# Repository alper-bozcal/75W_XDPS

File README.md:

# DBC2-Battery-Charger

  Main repository for the DEIF Battery Charger - 2 products.

## Dosyalama Sistemi

`Develop` branchinde kodun çalışma garantisi yoktur fakat en son kod bulunabilir. `Main` branch' de versiyon atlatıldığında stabil kod bulunabilir.

Yazılım `Firmware` klasöründe tutulmaktadır. `Common/` tüm ürünler için ortak fonksiyonları içermektedir. Bunun yanında yer alan klasörler ise proje ismine göre ayrılmıştır.

`ENKO` ve `Documents` klasörleri geliştirme sırasında oluşturulan dökümanları tutmaktadır. Bunları bazıları müşteri ile paylaşılmıştır.

`Hardware/` donanım şema ve PCB dosyalarını içermektedir.

`Simulations` ve `Tests` klasörleri donanım için gerekli çalışmalarda oluşturulan dosyaları içermektedir. Test sonuçları `Tests/` içerisinde bulunabilir.

## Algoritma

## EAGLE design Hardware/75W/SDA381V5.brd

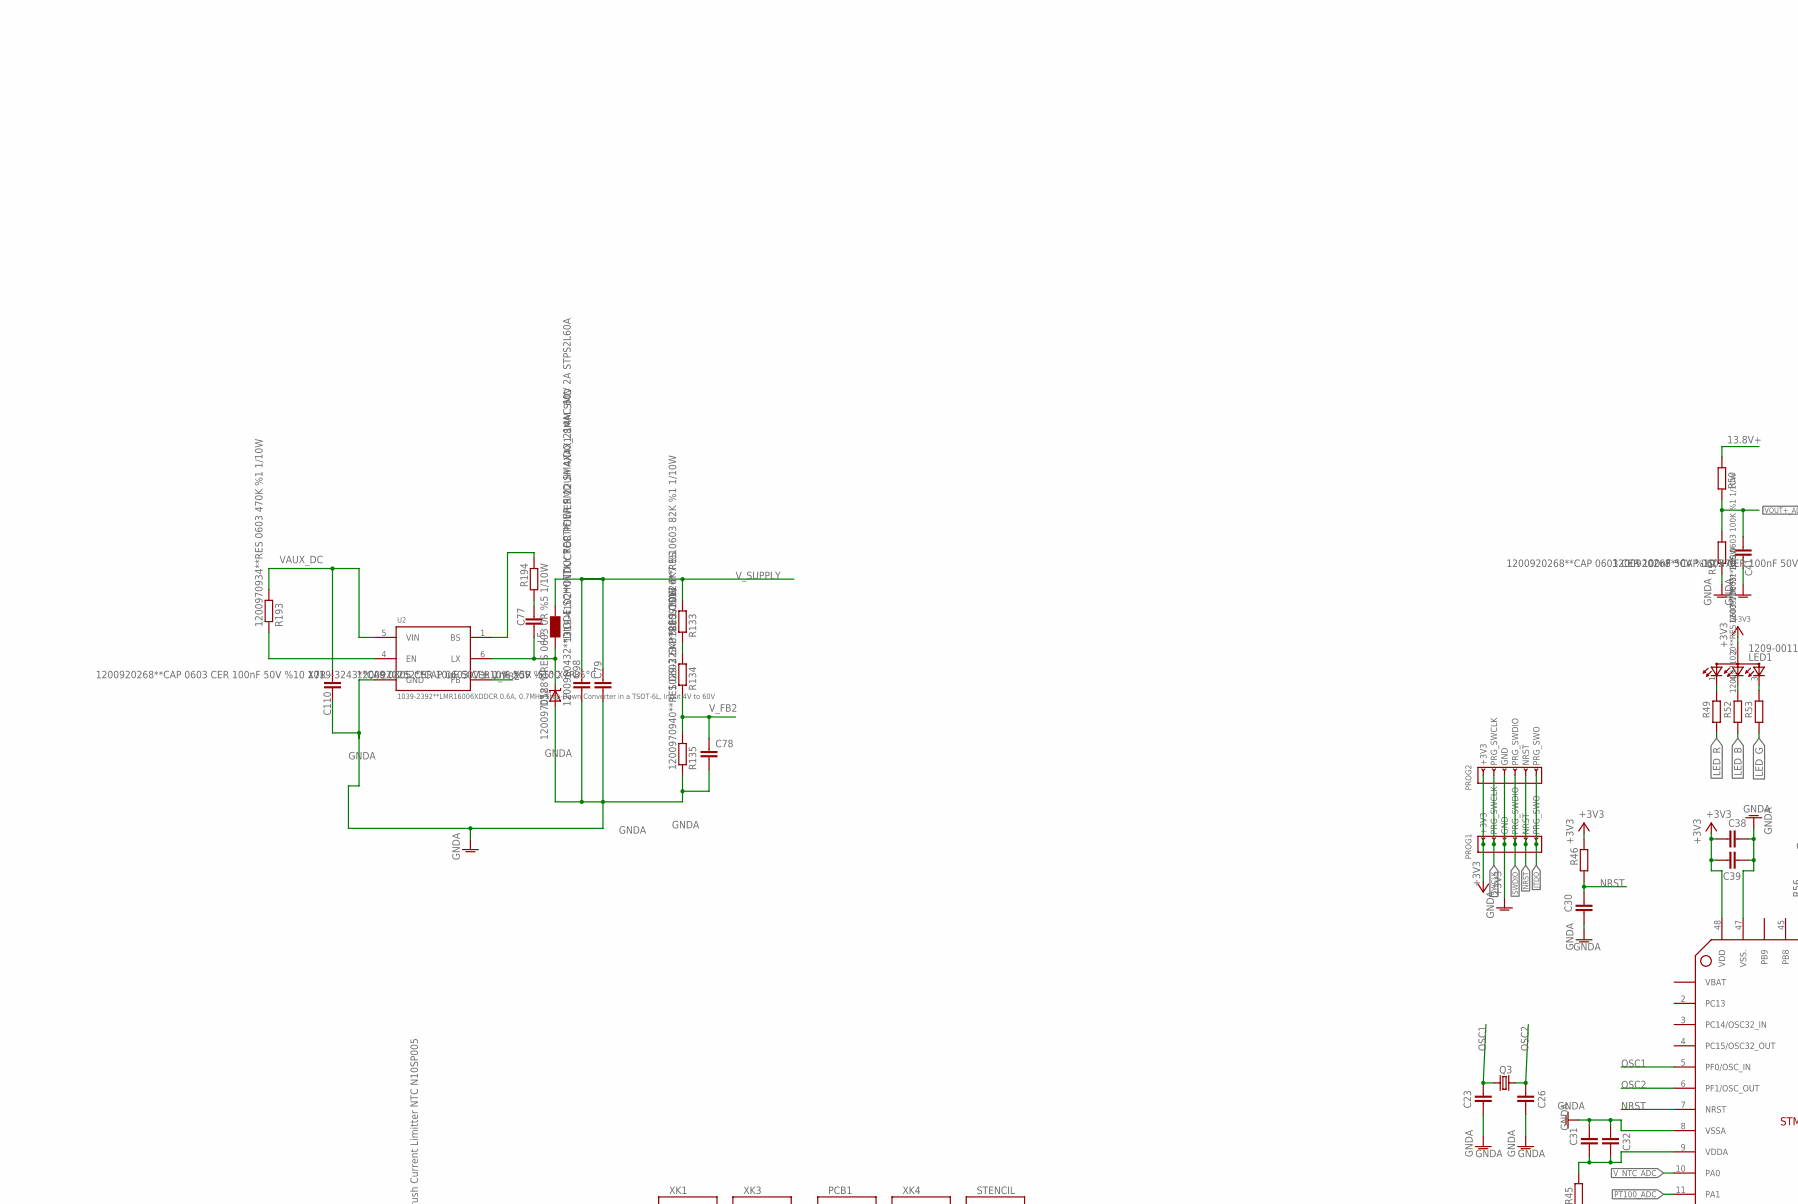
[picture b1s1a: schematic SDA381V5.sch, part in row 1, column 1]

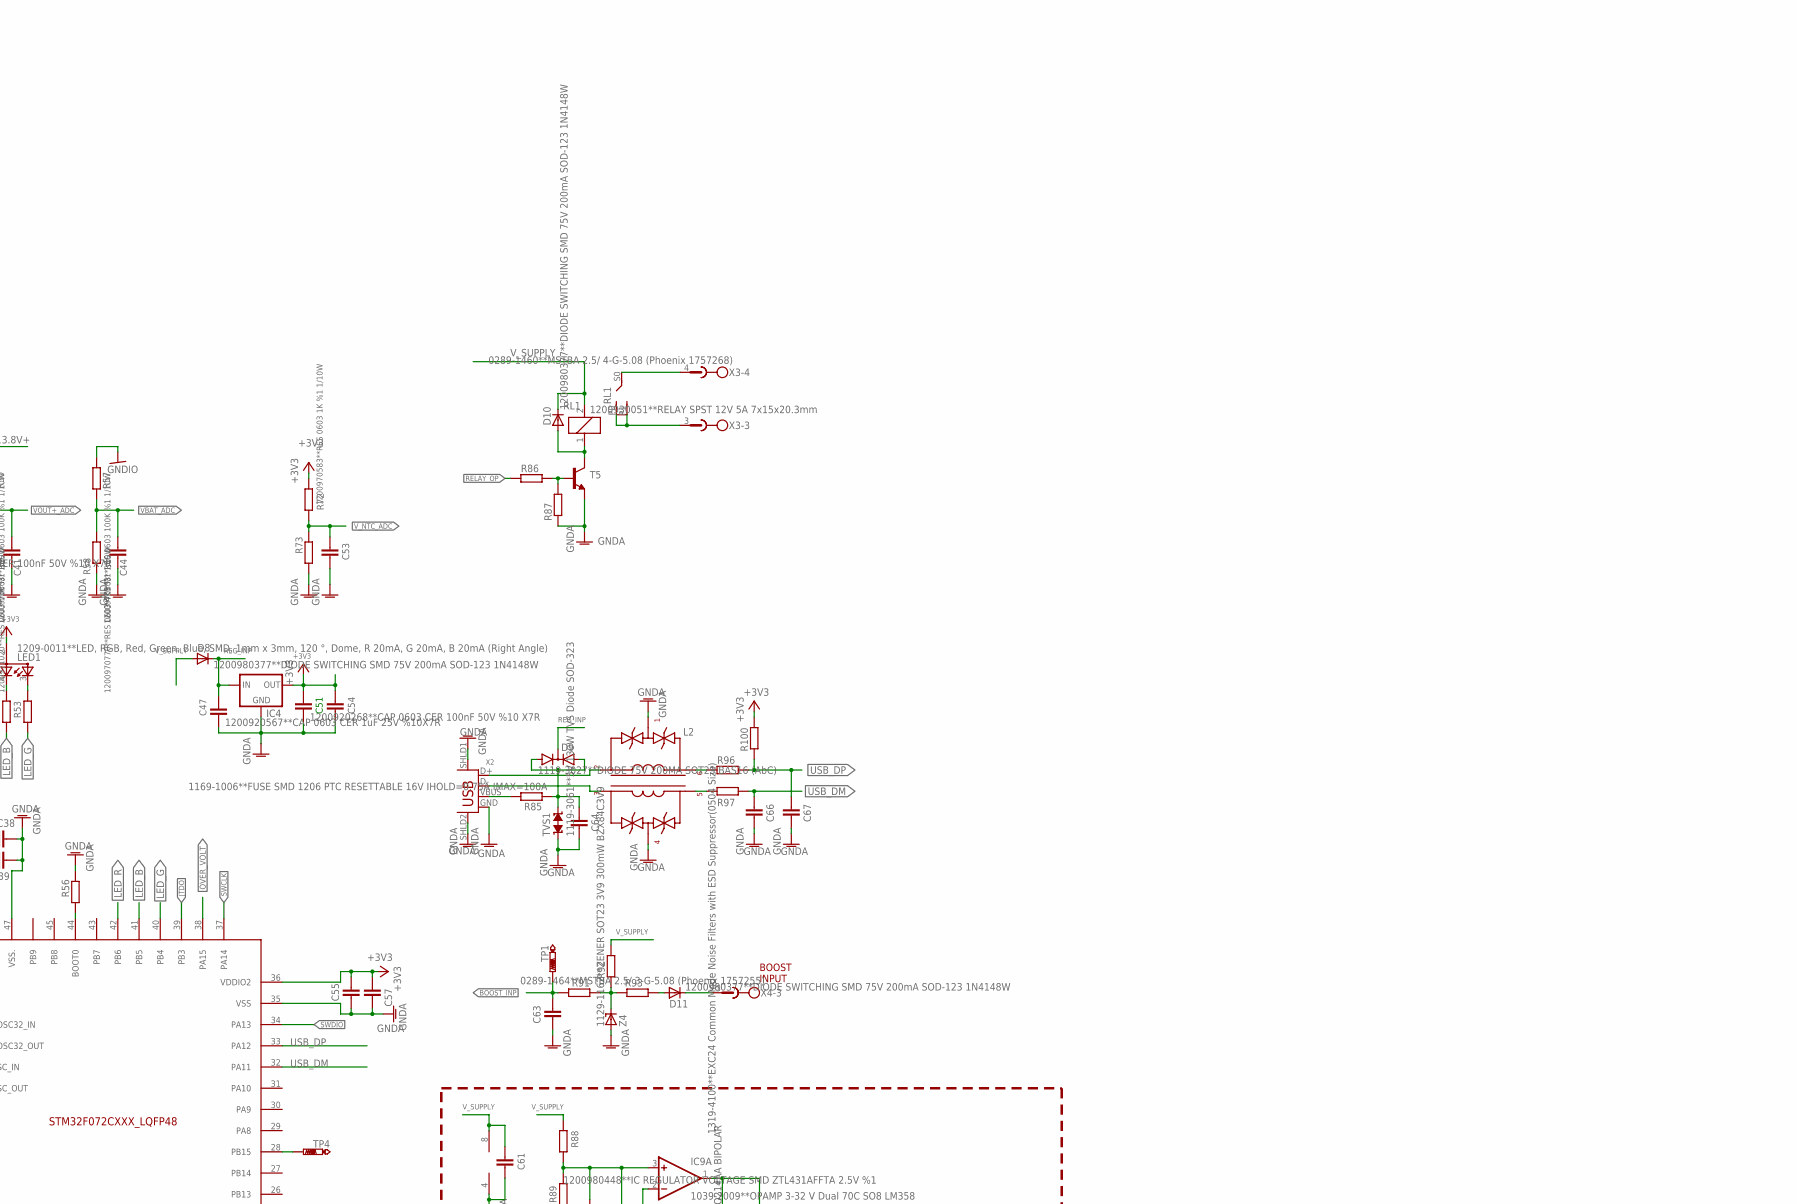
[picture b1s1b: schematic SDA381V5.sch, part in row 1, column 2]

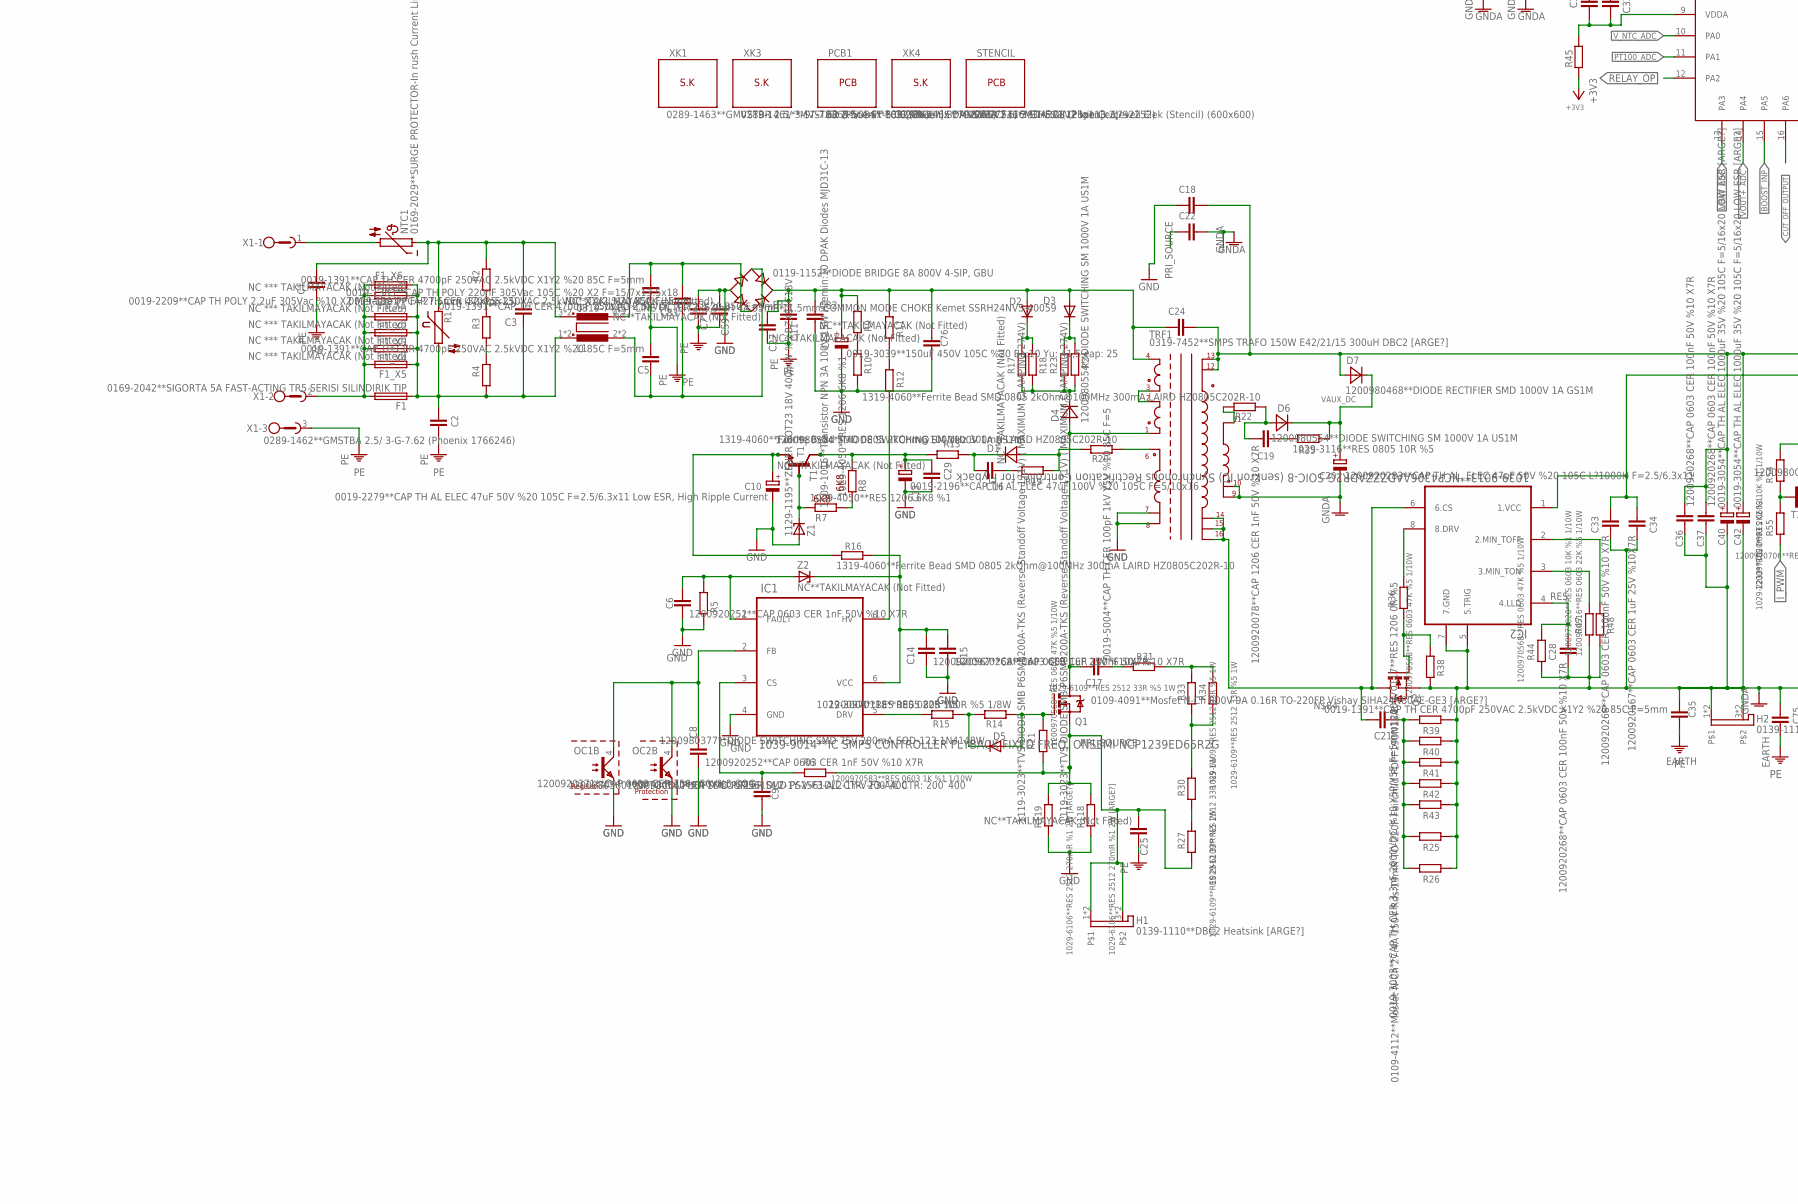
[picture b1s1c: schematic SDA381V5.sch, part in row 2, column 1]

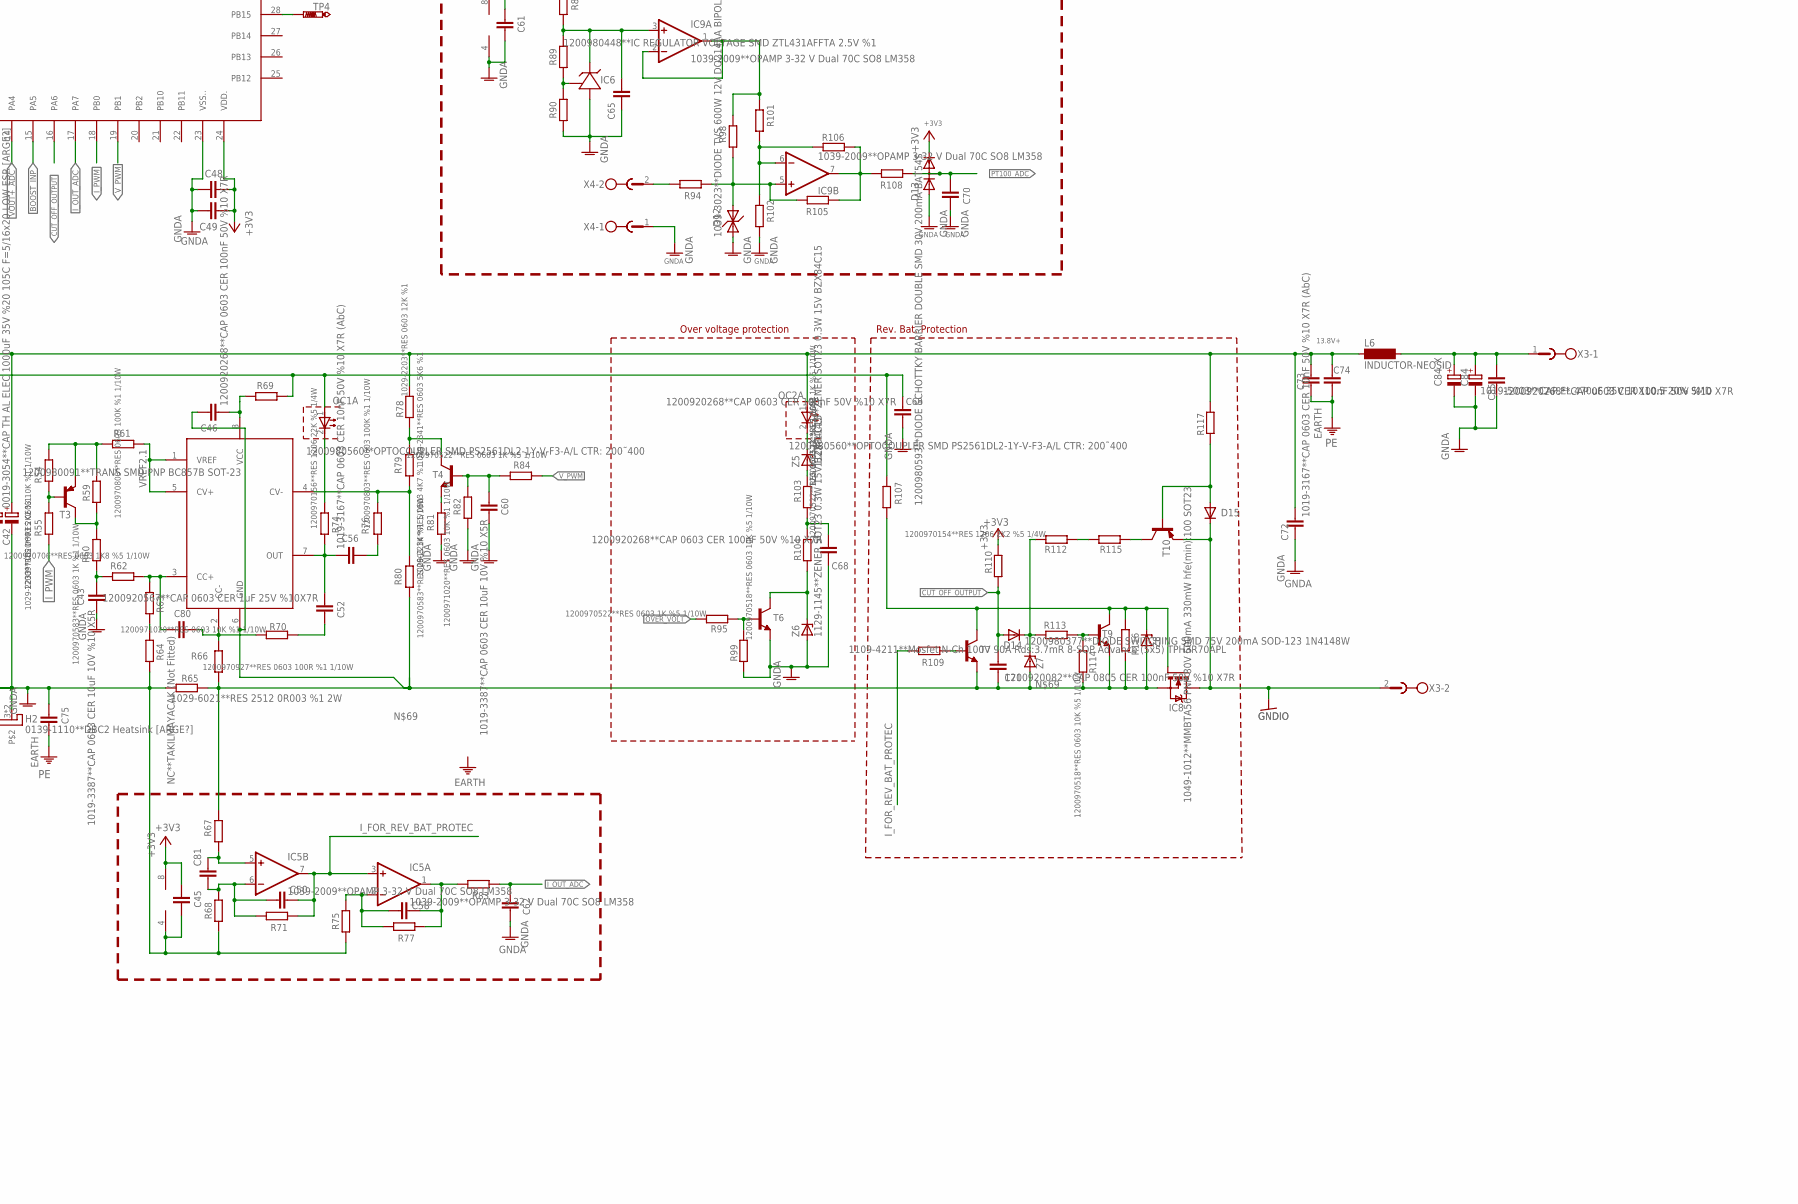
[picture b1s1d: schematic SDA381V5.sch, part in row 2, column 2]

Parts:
B1: 0119-1152**DIODE BRIDGE 8A 800V 4-SIP, GBU; DıODE_BRIDGE_8A_DIK
C1, C2, C25, C27, C59: NC**TAKILMAYACAK (Not Fitted); C50-035X75
C3: 0019-2209**CAP TH POLY 2.2uF 305Vac %10 X2 Metali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; C275-113X316_&_C150-072X183_&_C225-113X268
C4, C5, C7, C11: 0019-1391**CAP TH CER 4700pF 250VAC 2.5kVDC X1Y2 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; C50-035X75
C6, C8, C98: 1200920252**CAP 0603 CER 1nF 50V %10 X7R; C0603_ENKO
C9, C58: 1200920371**CAP 0603 CER 150p 50V%5 COG; C0603_ENKO
C10: 0019-2279**CAP TH AL ELEC 47uF 50V %20 105C F=2.5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; E2,5-7
C12: 0019-3039**150uF 450V 105C %20 Ba:10 Yu: 41,5 çap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; EB25D
C13: 0019-2196**CAP TH AL ELEC 47uF 100V %20 105C F=5/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; E5-10,5
C14, C34, C47, C52: 1200920567**CAP 0603 CER 1uF 25V %10X7R; C0603_ENKO
C15, C28, C30, C31, C33, C36, C37, C38, C41, C44, C45, C46, C49, C51, C53, C57, C61, C62, C64, C65, C68, C69, C70, C77, C85, C110: 1200920268**CAP 0603 CER 100nF 50V %10 X7R; C0603_ENKO
C16, C29: NC**TAKILMAYACAK (Not Fitted); C1206_ENKO
C17: 0019-5004**CAP TH CER 100pF 1kV Y5V %10 85C F=5; C075-32X103/C050-035X75
C18: 1200920292**CAP TH CER 2.2nF 300Vac %20 X1Y2 F=7.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; C075-32X103_DEIF
C19: 1200920078**CAP 1206 CER 1nF 50V %10 X7R; C1206_ENKO
C20: 1200920283**CAP TH AL. ELEC 47uF 50V %20 105C L?1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; E2,5-7
C21: 0019-3003**CAP TH CER 3.3nF 2000VDC %10 Y5P/Y5E F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; C050-045X075
C22, C24: NC**TAKILMAYACAK (Not Fitted); C075-32X103_DEIF
C23, C26: 1019-3352**CAP 0603 CER 22pF 50V %5 NPO; C0603_ENKO
C32, C39, C48, C55, C56, C63, C72: 1019-3167**CAP 0603 CER 10nF 50V %10 X7R (AbC); C0603_ENKO
C35: 0019-1391**CAP TH CER 4700pF 250VAC 2.5kVDC X1Y2 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; C050-045X075
C40: 0019-3054**CAP TH AL ELEC 1000uF 35V %20 105C F=5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; E5-13/E7,5-16
C42: 0019-3054**CAP TH AL ELEC 1000uF 35V %20 105C F=5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; E5-13
C43, C60: 1019-3387**CAP 0603 CER 10uF 10V %10 X5R; C0603_ENKO
C50, C80, C81: NC**TAKILMAYACAK (Not Fitted); C0603_ENKO
C54: 1019-3301**CAP 0805 47uF 6.3V %20 X5R; C0805_ENKO
C66, C67: 1019-3381**CAP 0603 CER 33pf 50V %5 NPO(COG); C0603_ENKO
C71: 1200920082**CAP 0805 CER 100nF 50V %10 X7R; C0805_ENKO
C73: 0019-1391**CAP TH CER 4700pF 250VAC 2.5kVDC X1Y2 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; C050-035X075
C74, C75: NC**TAKILMAYACAK (Not Fitted); C050-035X075
C76: NC**TAKILMAYACAK (Not Fitted); C065-052X106
C78: 1200920271**CAP 0603 CER 10pF 50V%10 COG; C0603_ENKO
C79: 1019-3243**CAP 0805 CER 10uF 50V ±10% X5R -55°C ~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; C0805_ENKO
C82: NC**TAKILMAYACAK (Not Fitted); C150-091X182
C83: 0019-1383**CAP TH POLY 220nF 305Vac 105C %20 X2 F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; C150-091X182_C225-108X268
C84: 1019-5003**CAP.EL.470uF 35V 10X10.5 20% SMD; E5-10,5
C84_X: CPOL-EUE2.5-7; E2,5-7
D1, D4, D6: 1200980554**DIODE SWITCHING SM 1000V 1A US1M; M7_DC_DIYOT
D2, D3: 1119-3023**TVS DIODE SMB P6SMB200A-TKS (Reverse S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; SMB
D5, D8, D10, D11, D14, D15: 1200980377**DIODE SWITCHING SMD 75V 200mA SOD-123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; SOD123
D7: 1200980468**DIODE RECTIFIER SMD 1000V 1A GS1M; M7_DC_DIYOT
D9: 1119-3027**DIODE 75V 200MA SOT23 BAS16 (AbC); SOT23
D12: 1039-3023**DIODE TVS 600W 12V DO214AA BIPOLAR; TRANSIL_SMB
D13: 1200980593**DIODE SCHOTTKY BARRIER DOUBLE SMD 30V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; SOT23
D18: 1200980432**DIODE SCHOTTKY RECTIFIER SMD SMA/DO_2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; SMA
F1: 0169-2042**SIGORTA 5A FAST-ACTING TR5 SERISI SILI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; SENS_FUSE
F1_X1: NC *** TAKILMAYACAK (Not Fitted); FUSE_0678D
F1_X2: NC *** TAKILMAYACAK (Not Fitted); FUSE_1025FA
F1_X3: NC *** TAKILMAYACAK (Not Fitted); FUSE_EBF_FUSE_446/447
F1_X4: NC *** TAKILMAYACAK (Not Fitted); FUSE_OMF250
F1_X5: NC *** TAKILMAYACAK (Not Fitted); FUSE_UMF250
F1_X6: FUSE_TYPE0679H
H1, H2: 0139-1110**DBC2 Heatsink [ARGE?]; DEIF_SOGUTUCU_2
IC1: 1039-9014**IC SMPS CONTROLLER FLYBACK FIXED FREQ.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; NCP1239_SMPS_IC
IC2: 1039-9013**NCP4306AADZZZADR2G SOIC-8 (senkron IC)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; NCP4306
IC3: 1039-2224**TSM1011ID SO-8 Constant Voltage and Co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; SO-8
IC4: 1039-3003**Voltage Regulator SOT-89 3.3V Diodes A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; SOT89
IC5, IC9: 1039-2009**OPAMP 3-32 V Dual 70C SO8 LM358; SO08
IC6: 1200980448**IC REGULATOR VOLTAGE SMD ZTL431AFFTA 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; TL431_SOT23F
IC8: 1109-4211**Mosfet N-Ch 100V 90A Rds:3.7mR 8-SOP A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; TPH6R30ANL
L1: 0319-7445**LINE FILTER 2x5,9mH 4A 55mR 11.5mm COM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; UU1620_&_FWCMET24V
L2: 1319-4100**EXC24 Common Mode Noise Filters with E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; EXC24CS_COMMON_MODE
L5: 1319-4102**INDUCTOR POWER 22UH 4X4X1.8MM SMD; WE-PD2_5MM
L6: INDUCTOR-NEOSID
LED1: 1209-0011**LED, RGB, Red, Green, Blue, SMD, 1mm x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; KPFA-3010RGBC-11
NTC1: 0169-2029**SURGE PROTECTOR-In rush Current Limitt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; NTC_15R_2A_&_N15SP005-5
OC1, OC2: 1200980560**OPTOCOUPLER SMD PS2561DL2-1Y-V-F3-A/L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; PS2561DL2-1_OPTO1
PCB1: 0369-5034**PCB [ARGE?] SDA381V2CF416M3HFS2(123x11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; PCB
PROG1, PROG2: NC**TAKILMAYACAK (Not Fitted); PROG_6PIN
Q1: 0109-4091**Mosfet N-Ch 800V 9A 0.16R TO-220FP Vis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; TO220BV
Q2: 0109-4112**Mosfet N-Ch 27.4A 150V Rds:19mR TO-220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; TO220BV
Q3: 1149-0006**HC49S SMD KRISTAL 8MHZ -40+85 20PF 50P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; HC49UP
R1: 0169-2013**Varistor 20mm 300V; S20K40
R2, R3, R4: 1200970587**RES 1206 470K %5 1/4W; R1206_ENKO
R5: 1200970687**RES 0603 56K %1 1/10W; R0603_ENKO
R6, R60, R61, R72, R75, R81, R89, R102: 1200970583**RES 0603 1K %1 1/10W; R0603_ENKO
R7, R8: 1029-4050**RES 1206 6K8 %1; R1206_ENKO
R9, R10: 1200970179**RES 1206 330K %5 1/4W; R1206_ENKO
R11, R12, R112: 1200970154**RES 1206 2K2 %5 1/4W; R1206_ENKO
R13: 1200970601**RES 1206 10R %5 1/4W; R1206_ENKO
R14: 1200970118**RES 0805 100R %5 1/8W; R0805_ENKO
R15: 1029-3008**RES 0805 22R %5; R0805_ENKO
R16, R20, R22, R45: 1319-4060**Ferrite Bead SMD 0805 2kOhm@100MHz 300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; R0805_ENKO
R17, R18, R23, R24: 1029-3146**RES 1206 7R68 %1; R1206_ENKO
R19: NC**TAKILMAYACAK (Not Fitted); R1206_ENKO
R21, R38, R44, R92: 1200970568**RES 0603 47K %5 1/10W; R0603_ENKO
R25, R26, R39, R40, R41, R42, R43: 1200970228**RES 1206 47R %5 1/4W; R1206_ENKO
R27, R30, R31, R33, R34: 1029-6109**RES 2512 33R %5 1W; R2512
R35, R69: 1029-3116**RES 0805 10R %5; R0805_ENKO
R36: 1200970117**RES 1206 0R %5; R1206_ENKO
R46, R87, R91, R99, R109, R114: 1200970518**RES 0603 10K %5 1/10W; R0603_ENKO
R47, R51, R54, R70, R82: 1200971020**RES 0603 10K %1 1/10W; R0603_ENKO
R48, R110: 1200970516**RES 0603 22K %5 1/10W; R0603_ENKO
R49, R52, R53: 1029-2005**RES 0603 220R %1; R0603_ENKO
R50, R57, R59, R76: 1200970803**RES 0603 100K %1 1/10W; R0603_ENKO
R55: 1029-2233**RES 0603 2K2 %1; R0603_ENKO
R56, R67, R68, R83, R84, R86, R95, R103, R104: 1200970522**RES 0603 1K %5 1/10W; R0603_ENKO
R58: 1200970770**RES 0603 4K3 %1 1/10W; R0603_ENKO
R62: 1200970706**RES 0603 1K8 %5 1/10W; R0603_ENKO
R63: 1029-2003**RES 0603 10R %1; R0603_ENKO
R64: 1029-2006**RES 0603 47R %1; R0603_ENKO
R65: 1029-6021**RES 2512 0R003 %1 2W; R2512
R66: 1200970927**RES 0603 100R %1 1/10W; R0603_ENKO
R71, R80, R88, R98, R134: 1029-2234**RES 0603 4K7 %1; R0603_ENKO
R73: 1169-1001**TSM2A103F3951RZ THINKING 0805 10K NTC 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; R0805_ENKO
R74: 1200970156**RES 1206 22K %5 1/4W; R1206_ENKO
R77: 1029-6089**RES 0603 6K8 %5; R0603_ENKO
R78: 1029-2203**RES 0603 12K %1; R0603_ENKO
R79: 1029-2341**RES 0603 5K6 %1; R0603_ENKO
R85: 1169-1006**FUSE SMD 1206 PTC RESETTABLE 16V IHOLD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; R1206_ENKO
R90: 1029-2231**RES 0603 1K8 %1; R0603_ENKO
R93: 1409-0025**RES 0603 470R %5 1/16W; R0603_ENKO
R94, R96, R97: 1029-6086**RES 0603 22R %1; R0603_ENKO
R100: 1200970852**RES 0603 1K5 %5 1/10W ( <-1029-3501 ); R0603_ENKO
R101: 1200970684**RES 0603 47K %1 1/10W; R0603_ENKO
R105: 1029-2229**RES 0603 120K %1; R0603_ENKO
R106: 1029-2219**RES 0603 30K %1; R0603_ENKO
R107: 1200970515**RES 0603 100K %5 1/10W; R0603_ENKO
R108: 1200970730**RES 0603 560R %1 1/10W; R0603_ENKO
R113: 1200970121**RES 0805 1K %5 1/8W; R0805_ENKO
R115: 1200970853**RES 1206 39K %1 1/4W; R1206_ENKO
R116: 1200970585**RES 0603 1M %5 1/10W; R0603_ENKO
R117: 1029-6015**RES 1206 56K %5; R1206_ENKO
R118, R119: 1029-6106**RES 2512 270mR %1 2W [ARGE?]; R2512
R133: 1200970626**RES 0603 82K %1 1/10W; R0603_ENKO
R135: 1200970940**RES 0603 6K8 %1 1/10W; R0603_ENKO
R193: 1200970934**RES 0603 470K %1 1/10W; R0603_ENKO
R194: 1200970528**RES 0603 0R %5 1/10W; R0603_ENKO
RL1: 1200930051**RELAY SPST 12V 5A 7x15x20.3mm; ALD1_AND_ALJ_RELAY
STENCIL: 041-7516**SDA381V2 için Çerçeveli Elek (Stencil) 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; PCB
T1: 1109-1016**Transistor NPN 3A 100V 15W Hfemin:10 D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; DPAK
T1_X, T4, T5, T6, T7, T9: 1200980090**TRANS SMD NPN BC847B SOT-23; SOT23
T3: 1200980091**TRANS SMD PNP BC857B SOT-23; SOT23-BEC
T10: 1049-1012**MMBTA56 PNP 80V 500mA 330mW hfe(min):1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; SOT23-BEC
TP1, TP4: PTR1TP20R; TP20R
TRF1: 0319-7452**SMPS TRAFO 150W E42/21/15 300uH DBC2 [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; DEIF_TRF
TVS1: 1119-3061**5V 130W TVS Diode SOD-323; SOD323
U1: 1039-2220**STM32F072C8T6 64K Flash USB, CAN; STM32F072CXXX_LQFP48
U2: 1039-2392**LMR16006XDDCR 0.6A, 0.7MHz Step-Down C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; AOZ1282CI-1
X1: 0289-1462**GMSTBA 2.5/ 3-G-7.62 (Phoenix 1766246); GMSTBA3
X2: 0309-1064**USB Type-B Mini Connector Horizantal; USB_B(YATIK)
X3: 0289-1460**MSTBA 2.5/ 4-G-5.08 (Phoenix 1757268); MSTBA4
X4: 0289-1464**MSTBA 2.5/ 3-G-5.08 (Phoenix 1757255); MSTBA3
XK1: 0289-1463**GMVSTBR 2.5/ 3-ST-7.62 (Phoenix 183253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; SOKET
XK3: 0289-1461**MVSTBR 2.5/ 4-ST-5.08 (Phoenix 1792265); SOKET
XK4: 0289-1465**MVSTBR 2.5/ 3-ST-5.08 (Phoenix 1792252); SOKET
Z1: 1129-1195**ZENER SOT23 18V 400mW %5 BZX84C18V; SOT23
Z2: NC**TAKILMAYACAK (Not Fitted); SOT23
Z4: 1129-1162**ZENER SOT23 3V9 300mW BZX84C3V9; SOT23
Z5, Z6: 1129-1145**ZENER SOT23 0.3W 15V BZX84C15; SOT23
Z7: 1129-1151**ZENER SOT23 12V 225mW BZX84C12; SOT23
Z8: 1129-1140**ZENER SOT23 5V1 0.4W BZX84C5V1; SOT23

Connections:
13.8V+: C18.P$1 (1), C24.P$1 (1), C36.1, C37.1, C40.+, C40.+1 (+), C42.+, C72.2, C73.1, C74.1, D7.A, L6.1, OC2.1, R50.1, R78.2, R117.1, TRF1.9 (12), TRF1.10 (13), TRF1.21 (13), TRF1.22 (12), TRF1.29 (12), TRF1.30 (13), TRF1.43 (12), TRF1.44 (13)
+3V3: C38.1, C39.1, C45.1, C48.1, C49.1, C51.1, C54.1, C55.1, C57.1, D13.2 (C), IC4.3 (OUT), IC5.8 (V+), LED1.2, PROG1.1 (+3V3), PROG2.1 (+3V3), R45.2, R46.1, R72.2, R100.2, R110.2, U1.24 (VDD.), U1.36 (VDDIO2), U1.48 (VDD)
AUX1: D1.A, R19.2, R20.2
BOOST_INP: C63.1, R91.1, TP1.TP, U1.15 (PA5)
CUT_OFF_OUTPUT: C71.1, D14.A, R110.1, U1.16 (PA6)
DRAIN1: C17.1, C17.3 (1), D4.A, Q1.D, TRF1.55 (1), TRF1.56 (1), TRF1.57 (1), TRF1.58 (1)
FB: C8.1, IC1.2 (FB), OC1.4, OC2.4
GATE1: IC8.GATE (G4), R107.1, R116.2, T7.3 (C), T9.3 (C), Z8.3 (C)
GND: B1.-, C6.2, C7.2, C8.2, C9.1, C10.-, C12.-, C13.-, C14.2, C15.2, C18.P$2 (2), C29.1, C59.2, C76.2, C82.2, IC1.4 (GND), OC1.3, OC2.3, R5.1, R10.1, R118.1, R119.1, TRF1.6 (7), TRF1.14 (7), TRF1.33 (7), TRF1.48 (8), TRF1.49 (7), Z1.1 (A)
GNDA: C20.-, C22.P$1 (1), C23.2, C26.2, C28.1, C30.1, C31.2, C32.2, C33.1, C34.1, C35.1, C36.2, C37.2, C38.2, C39.2, C40.-, C40.-1 (-), C41.2, C42.-, C43.1, C44.2, C45.2, C47.2, C48.2, C49.2, C51.2, C53.2, C54.2, C55.2, C57.2, C60.1, C61.2, C62.1, C63.2, C64.2, C65.1, C66.2, C67.2, C68.1, C69.1, C70.1, C72.1, C75.2, C78.2, C79.1, C84.-, C84_X.-, C85.2, C98.1, C110.1, D12.A1, D13.1 (A), D18.A, H2.1, H2.2, H2.3, H2.4, IC2.5 (5.TRIG), IC2.7 (7.GND), IC4.1 (GND), IC5.4 (V-), IC6.A (1), IC9.4 (V-), L2.1 (1.GND), L2.4 (4.GND), PROG1.3 (GND), PROG2.3 (GND), Q2.S, R25.2, R26.2, R38.2, R39.2, R40.2, R41.2, R42.2, R43.2, R44.2, R47.2, R48.2, R51.2, R56.1, R58.2, R64.1, R65.1, R68.1, R73.2, R75.1, R81.2, R82.2, R87.1, R90.1, R99.1, R102.1, R135.1, T5.2 (E), T6.2 (E), TRF1.6.1 (9), TRF1.6.2 (9), TRF1.6.5 (9), TRF1.7 (10), TRF1.24 (10), TRF1.27 (10), TRF1.40 (9), TRF1.41 (10), TVS1.A (1), U1.8 (VSSA), U1.23 (VSS..), U1.35 (VSS), U1.47 (VSS.), U2.2 (GND), X2.GND, X2.SHLD1 (1), X2.SHLD2 (2), X4.1, Z4.1 (A), Z6.1 (A)
GNDIO: D15.C, IC8.D (D5678), IC8.D1 (D5678), IC8.D2 (D5678), IC8.D3 (D5678), IC8.P$1 (D5678), IC8.P$2 (D5678), IC8.P$3 (D5678), R57.1, T10.E, X3.2
HV1: IC1.8 (HV), R12.2
I_FOR_REV_BAT_PROTEC: C50.2, IC5.3 (+IN), IC5.7 (OUT), R71.2, R109.2
I_OUT_ADC: C62.2, R83.2, U1.17 (PA7)
I_PWM: R55.2, U1.18 (PB0)
JTDO: PROG1.6 (PRG_SWO), PROG2.6 (PRG_SWO), U1.39 (PB3)
LED_B: R52.1, U1.41 (PB5)
LED_G: R53.1, U1.40 (PB4)
LED_R: R49.1, U1.42 (PB6)
unnamed: TRF1.1 (2), TRF1.2 (3), TRF1.17 (3), TRF1.18 (2), TRF1.36 (3), TRF1.37 (2), TRF1.53 (3), TRF1.54 (2)
unnamed: R63.1, R64.2
unnamed: Q2.G, R36.2, R38.1
unnamed: R30.2, R33.1, R34.1
unnamed: OC2.2, Z5.3 (C)
unnamed: D14.C, R112.2, R113.2, Z7.3 (C)
unnamed: B1.AC1, C4.2, C83.2, C83.4 (2), L1.4, L1.7 (4)
unnamed: R91.2, R92.2, R93.2, Z4.3 (C)
unnamed: R95.1, R99.2, T6.1 (B)
unnamed: D5.A, Q1.G, R14.1, R21.2
unnamed: R103.2, Z5.1 (A)
unnamed: IC6.R (2), R89.1, R90.2
unnamed: C19.1, R35.1
unnamed: C68.2, R103.1, R104.2
unnamed: C52.2, C56.2, IC3.7 (OUT), R74.1
unnamed: D11.A, R93.1
unnamed: D11.C, X4.3
unnamed: IC2.8 (8.DRV), R36.1
unnamed: R59.1, R60.1, T3.C
unnamed: C21.2, R25.1, R26.1, R39.1, R40.1, R41.1, R42.1, R43.1
unnamed: IC3.4 (CV-), R76.2, R79.1, R80.2
unnamed: C13.+, C29.2, R8.2, R13.1, T1.4 (C), T1_X.3 (C)
unnamed: C80.1, IC3.2 (CC-), R66.1, R70.2
unnamed: R94.1, X4.2
unnamed: L2.6, R96.1
unnamed: D2.C, R17.1, R18.1
unnamed: F1.2, F1_X1.P$2 (2), F1_X2.P$2 (2), F1_X3.P$2 (2), F1_X4.P$2 (2), F1_X5.P$2 (2), F1_X6.P$1 (1), X1.2
unnamed: C16.2, R19.1
unnamed: B1.AC2, C5.1, C83.1, C83.3 (1), L1.2, L1.6 (2)
unnamed: C17.2, C17.4 (2), R31.1
unnamed: C46.2, IC3.8 (VCC), R69.2
unnamed: C50.1, C81.1, IC5.6 (-IN), R68.2, R71.1
unnamed: C81.2, IC5.5 (+IN), R67.1
unnamed: C19.2, D6.A, R22.1
unnamed: R109.1, T7.1 (B)
unnamed: C10.+, R16.1, T1.3 (E), T1_X.2 (E)
unnamed: TP4.TP, U1.28 (PB15)
unnamed: IC2.2 (2.MIN_TOFF), R48.1
unnamed: D5.C, R14.2, R15.1
unnamed: C56.1, R76.1
unnamed: R78.1, R79.2, T4.3 (C)
unnamed: R81.1, T4.2 (E)
unnamed: IC1.5 (DRV), R15.2
unnamed: IC2.3 (3.MIN_TON), R47.1
unnamed: C60.2, R82.1, R84.2, T4.1 (B)
unnamed: C58.2, IC5.1 (OUT), R77.2, R83.1
unnamed: R54.1, R59.2, R61.1, T3.E
unnamed: LED1.1, R49.2
unnamed: C43.2, R60.2, R62.2
unnamed: C80.2, IC3.3 (CC+), R62.1, R63.2
unnamed: R54.2, R55.1, T3.B
unnamed: C58.1, IC5.2 (-IN), R75.2, R77.1
unnamed: R104.1, T6.3 (C), Z6.3 (C)
unnamed: D3.C, R23.1, R24.1
unnamed: R56.2, U1.44 (BOOT0)
unnamed: C46.1, C71.2, IC3.6 (GND), IC8.S (S123), IC8.S1 (S123), IC8.S2 (S123), R65.2, R66.2, R67.2, R80.1, R114.2, R116.1, T7.2 (E), T9.2 (E), Z7.1 (A), Z8.1 (A)
unnamed: C77.2, D18.C, L5.2 (1), U2.6 (LX)
unnamed: C77.1, R194.2
unnamed: R194.1, U2.1 (BS)
unnamed: R193.1, U2.4 (EN)
unnamed: R20.1, TRF1.5 (6), TRF1.15 (6), TRF1.34 (6), TRF1.50 (6)
unnamed: R31.2, R33.2, R34.2
unnamed: R22.2, TRF1.8 (11), TRF1.23 (11), TRF1.28 (11), TRF1.42 (11)
unnamed: RL1.S0, X3.4
unnamed: C1.2, C3.2, C3.4 (2), C3.6 (2), L1.3, L1.8 (3), NTC1.P$1 (1), NTC1.P$4 (1), R1.1, R2.1
unnamed: C2.2, C3.1, C3.3 (1), C3.5 (1), F1.1, F1_X1.P$1 (1), F1_X2.P$1 (1), F1_X3.P$1 (1), F1_X4.P$1 (1), F1_X5.P$1 (1), F1_X6.P$2 (2), L1.1, L1.5 (1), R1.2, R4.2
unnamed: R112.1, R115.1
unnamed: C21.1, IC2.6 (6.CS), Q2.D, TRF1.11 (14), TRF1.12 (15), TRF1.13 (16), TRF1.19 (15), TRF1.20 (14), TRF1.25 (16), TRF1.31 (14), TRF1.32 (15), TRF1.38 (16), TRF1.45 (14), TRF1.46 (15), TRF1.47 (16)
unnamed: C84.+, C84_X.+, C85.1, L6.2, X3.1
unnamed: R27.2, R30.1
unnamed: NTC1.P$2 (2), NTC1.P$3 (2), X1.1
unnamed: D15.A, R117.2, T10.B
unnamed: D4.C, R17.2, R18.2, R23.2, R24.2
unnamed: C31.1, C32.1, R45.1, U1.9 (VDDA)
unnamed: R2.2, R3.2
unnamed: R3.1, R4.1
unnamed: LED1.4, R52.2
unnamed: LED1.3, R53.2
unnamed: R9.1, R10.2
unnamed: R115.2, T10.C
unnamed: IC9.6 (-IN), R101.1, R102.2, R106.1
unnamed: D12.A, IC9.5 (+IN), R94.2, R98.1, R105.1
unnamed: R113.1, R114.1, T9.1 (B)
unnamed: IC9.7 (OUT), R105.2, R106.2, R108.1
unnamed: D10.A, RL1.1, T5.3 (C)
unnamed: R86.1, R87.2, T5.1 (B)
unnamed: L2.5, R97.1
unnamed: C65.2, IC6.C (3), IC9.3 (+IN), R88.1, R89.2
unnamed: IC9.1 (OUT), IC9.2 (-IN), R98.2, R101.2
unnamed: C16.1, D1.C, R13.2
unnamed: R11.1, R12.1
unnamed: C6.1, IC1.1 (FAULT), R5.2, Z2.1 (A)
unnamed: R133.1, R134.2
unnamed: L2.3, X2.D-
unnamed: L2.2, X2.D+
unnamed: C64.1, D9.1 (A1), D9.2 (A2), R85.1, TVS1.C (2)
unnamed: R7.2, R8.1
unnamed: R7.1, T1.1 (B), T1_X.1 (B), Z1.3 (C)
unnamed: C52.1, R70.1
NRST: C30.2, PROG1.5 (NRST), PROG2.5 (NRST), R46.2, U1.7 (NRST)
OSC1: C23.1, Q3.1, U1.5 (PF0/OSC_IN)
OSC2: C26.1, Q3.2, U1.6 (PF1/OSC_OUT)
OVER_VOLT: R95.2, U1.38 (PA15)
PE: C1.1, C2.1, C4.1, C5.2, C7.1, C11.1, C25.1, C27.1, C35.2, C59.1, C73.2, C74.2, C75.1, X1.3
PRI_SOURCE: C22.P$2 (2), C25.2, H1.1, H1.2, H1.3, H1.4, Q1.S, R6.2, R21.1, R27.1, R118.2, R119.2
PT100_ADC: C70.2, D13.3 (AC), R108.2, U1.11 (PA1)
REG_INP: C47.1, D8.C, D9.3 (C), IC4.2 (IN), IC4.4 (IN)
RELAY_OP: R86.2, U1.12 (PA2)
RES: C28.2, IC2.4 (4.LLD), R44.1
RL+: RL1.P0, RL1.P1, X3.3
SENSE: C9.2, IC1.3 (CS), R6.1
SWCLK: PROG1.2 (PRG_SWCLK), PROG2.2 (PRG_SWCLK), U1.37 (PA14)
SWDIO: PROG1.4 (PRG_SWDIO), PROG2.4 (PRG_SWDIO), U1.34 (PA13)
U3-K: OC1.2, R74.2
USB_DM: C66.1, R97.2, U1.32 (PA11)
USB_DP: C67.1, R96.2, R100.1, U1.33 (PA12)
VAUX_DC: C20.+, C110.2, D6.C, D7.C, R35.2, R193.2, U2.5 (VIN)
VAUX_PRI: C14.1, C15.1, IC1.6 (VCC), R16.2, Z2.3 (C)
VBAT_ADC: C44.1, R57.2, R58.1, U1.13 (PA3)
VBUS1: R85.2, X2.VBUS
VDC_BUS: B1.+, C11.2, C12.+, C24.P$2 (2), C27.2, C76.1, C82.1, D2.A, D3.A, R9.2, R11.2, TRF1.3 (4), TRF1.16 (4), TRF1.35 (4), TRF1.52 (4)
VOUT+_ADC: C41.1, R50.2, R51.1, U1.14 (PA4)
VREF2.1: IC3.1 (VREF), IC3.5 (CV+), R61.2
V_FB2: C78.1, R134.1, R135.2, U2.3 (FB)
V_NTC_ADC: C53.1, R72.1, R73.1, U1.10 (PA0)
V_PWM: R84.1, U1.19 (PB1)
V_SUPPLY: C33.2, C34.2, C61.1, C69.2, C79.2, C98.2, D8.A, D10.C, IC2.1 (1.VCC), IC9.8 (V+), L5.1 (2), OC1.1, R69.1, R88.2, R92.1, R107.2, R133.2, RL1.2

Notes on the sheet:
Rev. Bat. Protection
Over voltage protection
HV Protection
Regulation
BOOST INPUT
6K8

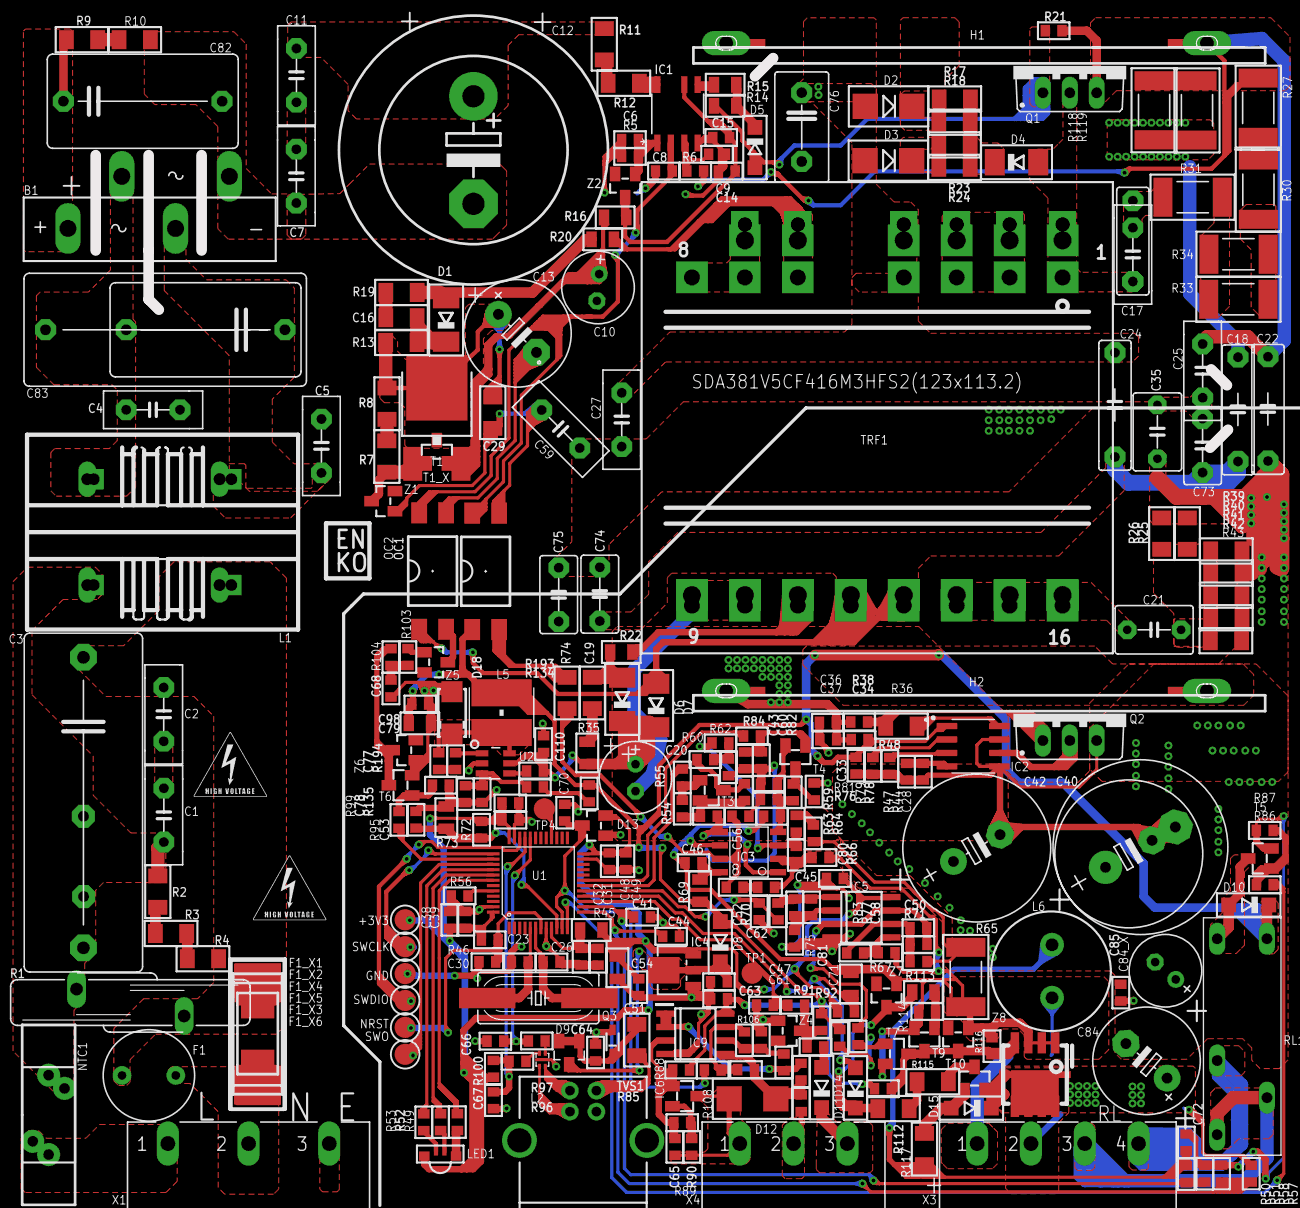
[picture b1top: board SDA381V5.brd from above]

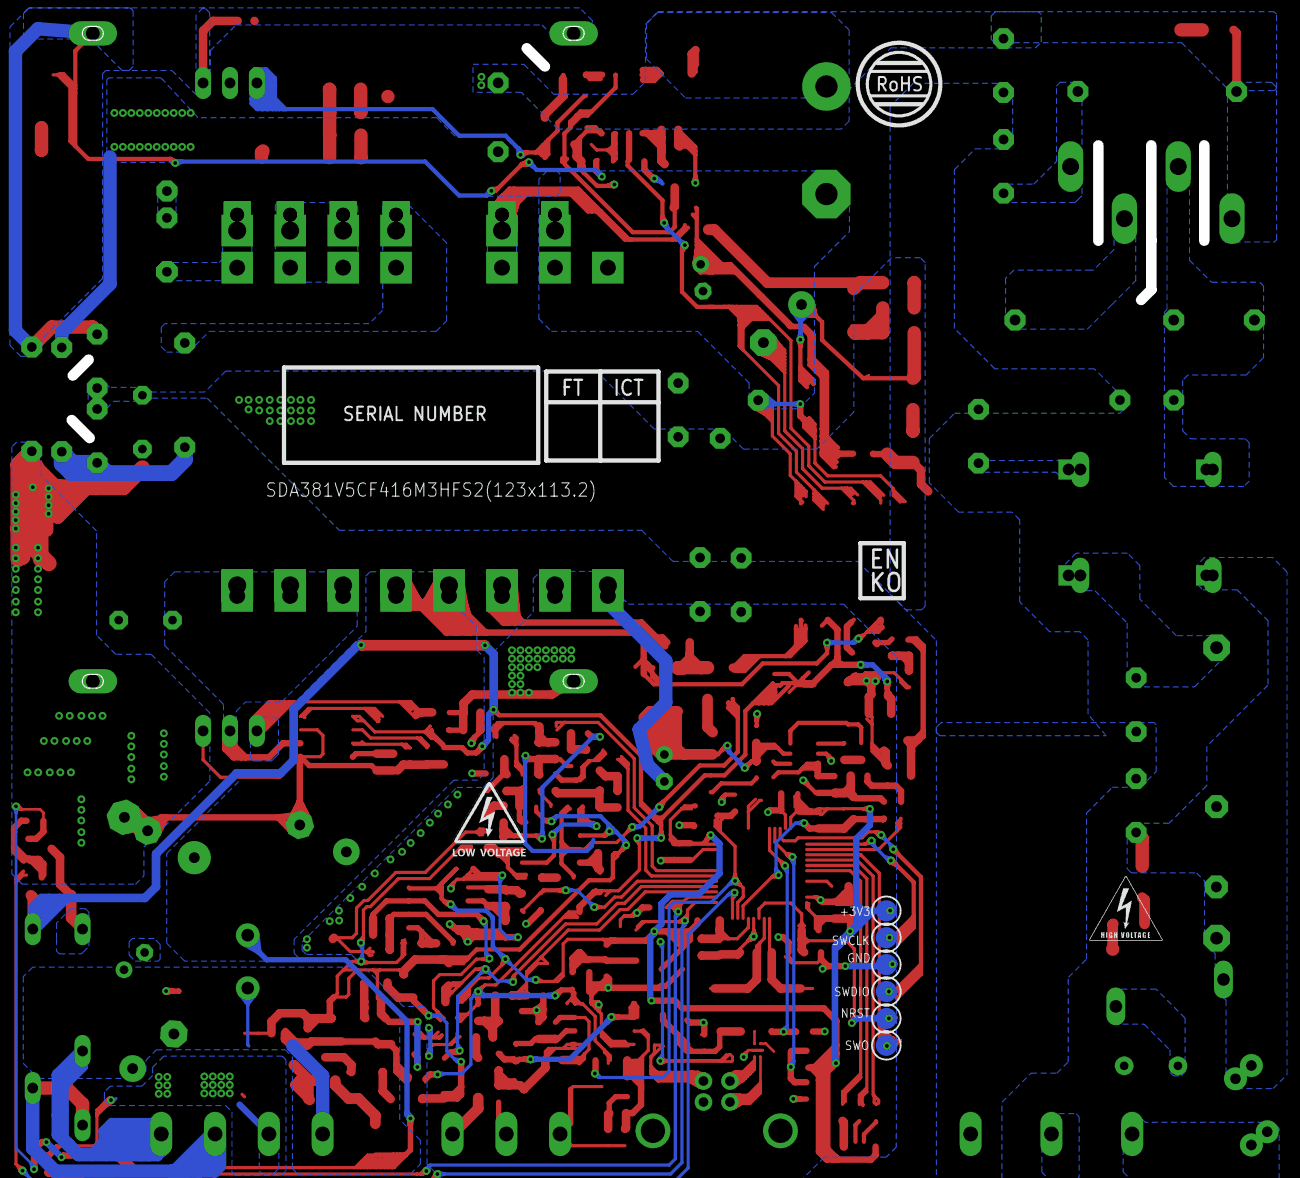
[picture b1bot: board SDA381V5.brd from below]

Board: 2 copper layers, 291 parts (5 on the bottom side), 146 nets.

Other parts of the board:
U$1: SERI_NO_ETIKET_ALANI
U$2, U$3: EN-KO_AMLEMI
U$4: ROHS
U$5: FT-ICT

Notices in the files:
parts and their libraries:
SparkFun-PowerSymbols: Licensing: Creative Commons ShareAlike 4.0 International - https://creativecommons.org/licenses/by-sa/4.0
supressor: Copyright (C) 2009, Bob Starr
op-amp: Copyright (C) 2015, Bob Starr
wuerth-elektronik: Copyright: Würth Elektronik eiSos
